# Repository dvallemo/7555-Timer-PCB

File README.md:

# Getting to Blinky 5.0

A two-layer PCB designed in KiCad featuring a 7555 CMOS timer astable oscillator circuit that blinks an LED. Built as a hands-on learning project to develop familiarity with KiCad schematic capture, footprint assignment, PCB layout, and DRC workflow.

---

## Circuit Overview

The circuit uses a 7555 timer (U1) configured in **astable mode** to generate a continuous square wave output that drives an LED.

| Ref | Part | Value | Description |
|-----|------|-------|-------------|
| U1 | 7555 Timer | - | SO-8 SMD package, custom schematic symbol |
| BT1 | CR2032 | 3V | Coin cell battery, custom PCB footprint |
| R1 | Resistor | 1k ohm | Timing resistor (charge path) |
| R2 | Resistor | 470k ohm | Timing resistor (discharge path) |
| R3 | Resistor | 1k ohm | LED current limiting resistor |
| C1 | Capacitor | 1uF | Timing capacitor |
| D1 | LED | - | Output indicator, 0805 SMD |

### How It Works

The 7555 timer alternately charges and discharges C1 through R1 and R2, producing a square wave on the OUT pin (pin 3). R3 limits current through D1. The blink frequency is approximately:

```
f = 1.44 / ((R1 + 2*R2) * C1)
f = 1.44 / ((1k + 2*470k) * 1uF) = 1.53 Hz
```

---

## PCB Details

- **Tool:** KiCad 8
- **Layers:** 2-layer board
- **Power supply:** CR2032 coin cell (3V)
- **Trace width:** 0.2mm for improved manufacturability
- **Copper pours:** GND pour on B.Cu, VDD pour on F.Cu
- **Package sizes:** All passives in 0805 for hand solderability

### Custom Work

- **Custom schematic symbol** created for the 7555 timer (U1)
- **Custom PCB footprint** created for the CR2032 coin cell holder (BT1)

### DRC Results

| Category | Count |
|----------|-------|
| Errors | 0 |
| Warnings | 4 |
| Unconnected Items | 0 |

The 4 warnings are non-critical: 3 are single-layer via warnings resolved after copper pour fill, and 1 is a footprint-library mismatch on BT1 due to the custom footprint.

---

## Board Images

### Schematic

### Assigning Footprints

### PCB Layout

### 3D Render - Top

### 3D Render - Bottom

---

## Key Learnings

- KiCad schematic capture and ERC workflow
- Creating custom schematic symbols and PCB footprints
- 7555 CMOS timer astable configuration and timing calculations
- Two-layer PCB layout with copper pour fills
- DRC execution and warning triage
- Silkscreen labeling and board branding

---

## Author

**Dave** - Electrical Engineering, Stevens Institute of Technology  
PCB design portfolio project | KiCad | June 2026

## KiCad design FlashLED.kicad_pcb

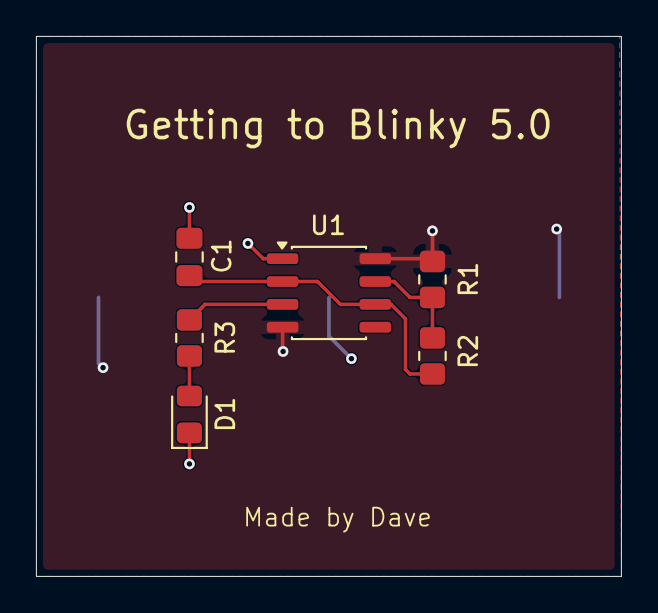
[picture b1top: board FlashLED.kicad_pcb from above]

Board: 2 copper layers, 32.5 x 30.0 mm, 7 parts (1 on the bottom side), 6 nets.

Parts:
BT1: CR2032; S8211-46R
C1: 1uF; C_0805_2012Metric_Pad1.18x1.45mm_HandSolder
D1: LED; LED_0805_2012Metric_Pad1.15x1.40mm_HandSolder
R1, R3: 1k; R_0805_2012Metric_Pad1.20x1.40mm_HandSolder
R2: 470k; R_0805_2012Metric_Pad1.20x1.40mm_HandSolder
U1: SO-8_3.9x4.9mm_P1.27mm

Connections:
/DIS: R1.2, R2.1, U1.7 (DIS)
/OUT: R3.1, U1.3 (OUT)
/TRIG: C1.1, R2.2, U1.2 (~Trig), U1.6 (TRSH)
/VDD: BT1.1 (-_2), BT1.2 (+_1), R1.1, U1.4 (~RST), U1.8 (VDD)
GND: BT1.GND, C1.2, D1.1 (K), U1.1 (GND)
unnamed: D1.2 (A), R3.2

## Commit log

2026-06-24 Create images
2026-06-24 Create test
2026-06-24 Rename Screenshot 2026-06-24 101319.png to layout
2026-06-24 Rename layout to layout.png
2026-06-24 Rename Screenshot 2026-06-24 101424.png to footprints.png
2026-06-24 Rename Screenshot 2026-06-24 101358.png to Schematic.png
2026-06-24 Rename Screenshot 2026-06-24 101348.png to 3D_Bottom
2026-06-24 Rename Screenshot 2026-06-24 101336.png to 3D_Top
2026-06-24 Rename 3D_Bottom to 3D_Bottom.png
2026-06-24 Rename 3D_Top to 3D_Top.png
